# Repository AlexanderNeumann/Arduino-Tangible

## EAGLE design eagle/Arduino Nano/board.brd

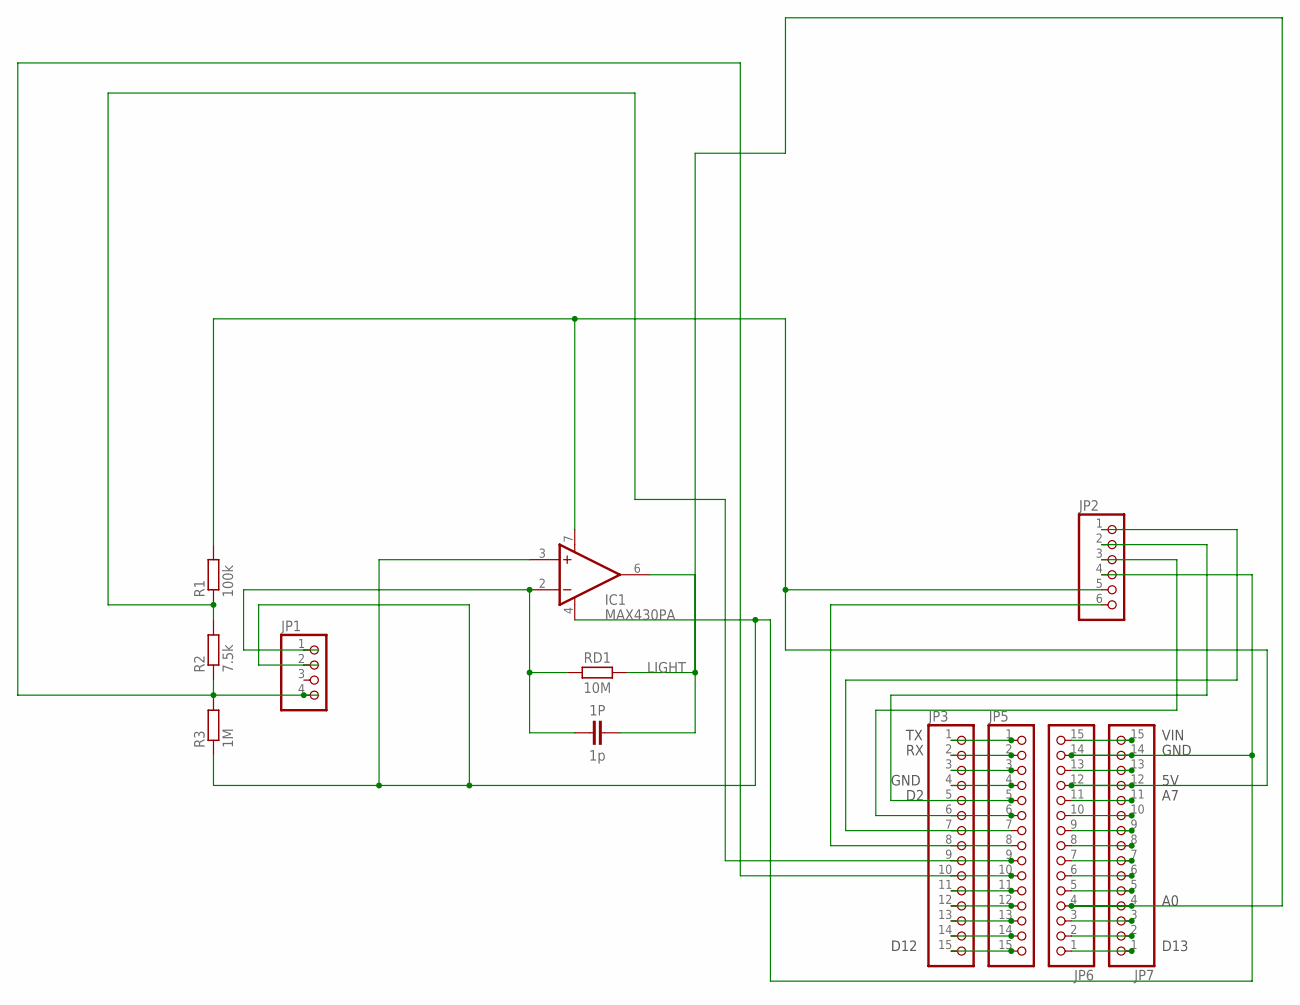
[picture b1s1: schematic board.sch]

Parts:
1P: 1p; 1206
IC1: MAX430PA; DIL08
JP1: PINHD-1X4; 1X04
JP2: PINHD-1X6; 1X06
JP3, JP5, JP6, JP7: PINHD-1X15; 1X15
R1: 100k; R1206
R2: 7.5k; R1206
R3: 1M; R1206
RD1: 10M; 1206

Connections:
LIGHT: 1P.2, IC1.6 (OUT), JP6.4, JP7.4, RD1.2
unnamed: JP3.9, JP5.9, R1.1, R2.2
unnamed: JP1.4, JP3.10, JP5.10, R2.1, R3.2
unnamed: JP2.1, JP3.7, JP5.7
unnamed: JP2.2, JP3.5, JP5.5
unnamed: IC1.3 (+IN), IC1.4 (V-), JP1.2, JP2.4, JP6.14, JP7.14, R3.1
unnamed: JP6.1, JP7.1
unnamed: JP6.2, JP7.2
unnamed: 1P.1, IC1.2 (-IN), JP1.1, RD1.1
unnamed: JP2.6, JP3.8, JP5.8
unnamed: JP2.3, JP3.6, JP5.6
unnamed: JP6.3, JP7.3
unnamed: JP6.5, JP7.5
unnamed: JP6.6, JP7.6
unnamed: JP6.7, JP7.7
unnamed: JP6.8, JP7.8
unnamed: JP6.9, JP7.9
unnamed: JP6.10, JP7.10
unnamed: JP6.11, JP7.11
unnamed: JP6.13, JP7.13
unnamed: JP6.15, JP7.15
unnamed: JP3.3, JP5.3
unnamed: JP3.4, JP5.4
unnamed: JP3.11, JP5.11
unnamed: JP3.12, JP5.12
unnamed: JP3.13, JP5.13
unnamed: JP3.14, JP5.14
unnamed: JP3.15, JP5.15
unnamed: JP3.1, JP5.1
unnamed: JP3.2, JP5.2
V0_3V3_1A0: IC1.7 (V+), JP2.5, JP6.12, JP7.12, R1.2

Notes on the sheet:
D12
VIN
GND
D13

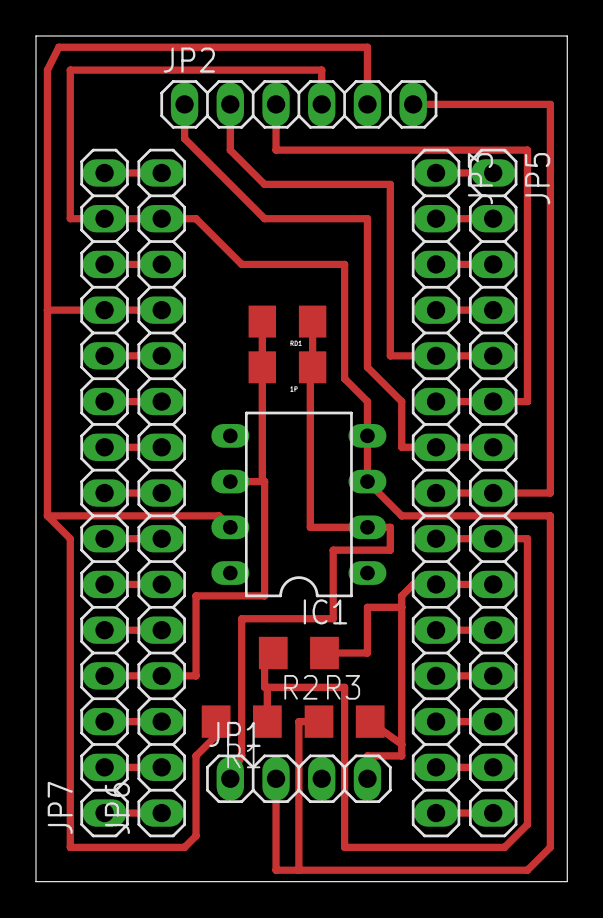
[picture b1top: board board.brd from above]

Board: 2 copper layers, 29.5 x 47.0 mm, 12 parts (0 on the bottom side), 31 nets.

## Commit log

2016-07-25 first commit
    nano shield design and case, Arduino template
2016-07-26 case
2016-07-26 name change
2016-07-26 CircuitCam files
2016-08-08 one file
2016-08-08 boardmaster file
